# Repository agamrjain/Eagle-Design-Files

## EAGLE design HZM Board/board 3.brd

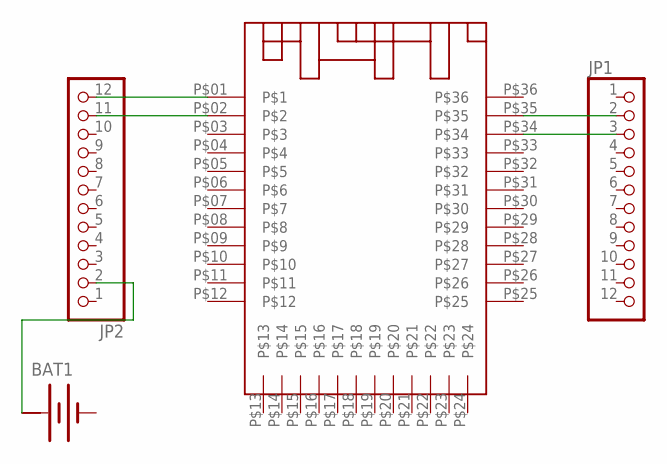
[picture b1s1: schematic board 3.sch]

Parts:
BAT1: BATTERY
JP1: PINHD-1X12; 1X12
JP2: PINHD-1X12/90; 1X12/90
U$1: HZX_MODULE; SMD_PAD_VERSION

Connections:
+: BAT1.+@1 (+)
-: BAT1.-
unnamed: BAT1.+, JP2.2
unnamed: JP2.11, U$1.P$02
unnamed: JP2.12, U$1.P$01
unnamed: JP1.2, U$1.P$35
unnamed: JP1.3, U$1.P$34

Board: 2 copper layers, 4 parts (0 on the bottom side), 5 nets, no tracks yet.

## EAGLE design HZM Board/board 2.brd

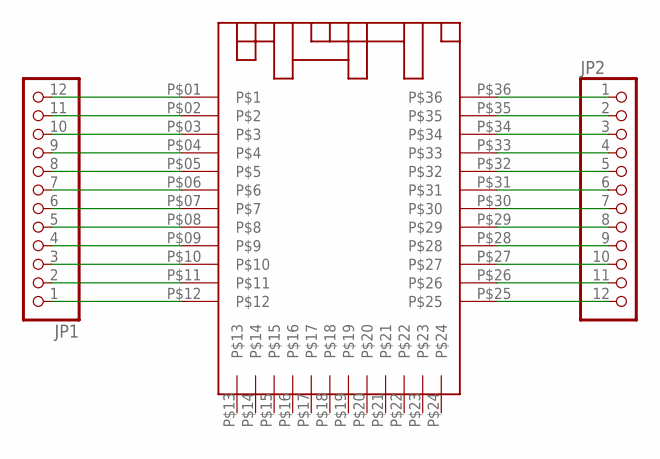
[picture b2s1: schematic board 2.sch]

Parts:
JP1, JP2: PINHD-1X12; 1X12
U$1: HZX_MODULE; SMD_PAD_VERSION

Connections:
unnamed: JP1.1, U$1.P$12
unnamed: JP1.2, U$1.P$11
unnamed: JP1.3, U$1.P$10
unnamed: JP1.4, U$1.P$09
unnamed: JP1.5, U$1.P$08
unnamed: JP1.6, U$1.P$07
unnamed: JP1.7, U$1.P$06
unnamed: JP1.8, U$1.P$05
unnamed: JP1.9, U$1.P$04
unnamed: JP1.10, U$1.P$03
unnamed: JP1.11, U$1.P$02
unnamed: JP1.12, U$1.P$01
unnamed: JP2.1, U$1.P$36
unnamed: JP2.2, U$1.P$35
unnamed: JP2.3, U$1.P$34
unnamed: JP2.4, U$1.P$33
unnamed: JP2.5, U$1.P$32
unnamed: JP2.6, U$1.P$31
unnamed: JP2.7, U$1.P$30
unnamed: JP2.8, U$1.P$29
unnamed: JP2.9, U$1.P$28
unnamed: JP2.10, U$1.P$27
unnamed: JP2.11, U$1.P$26
unnamed: JP2.12, U$1.P$25

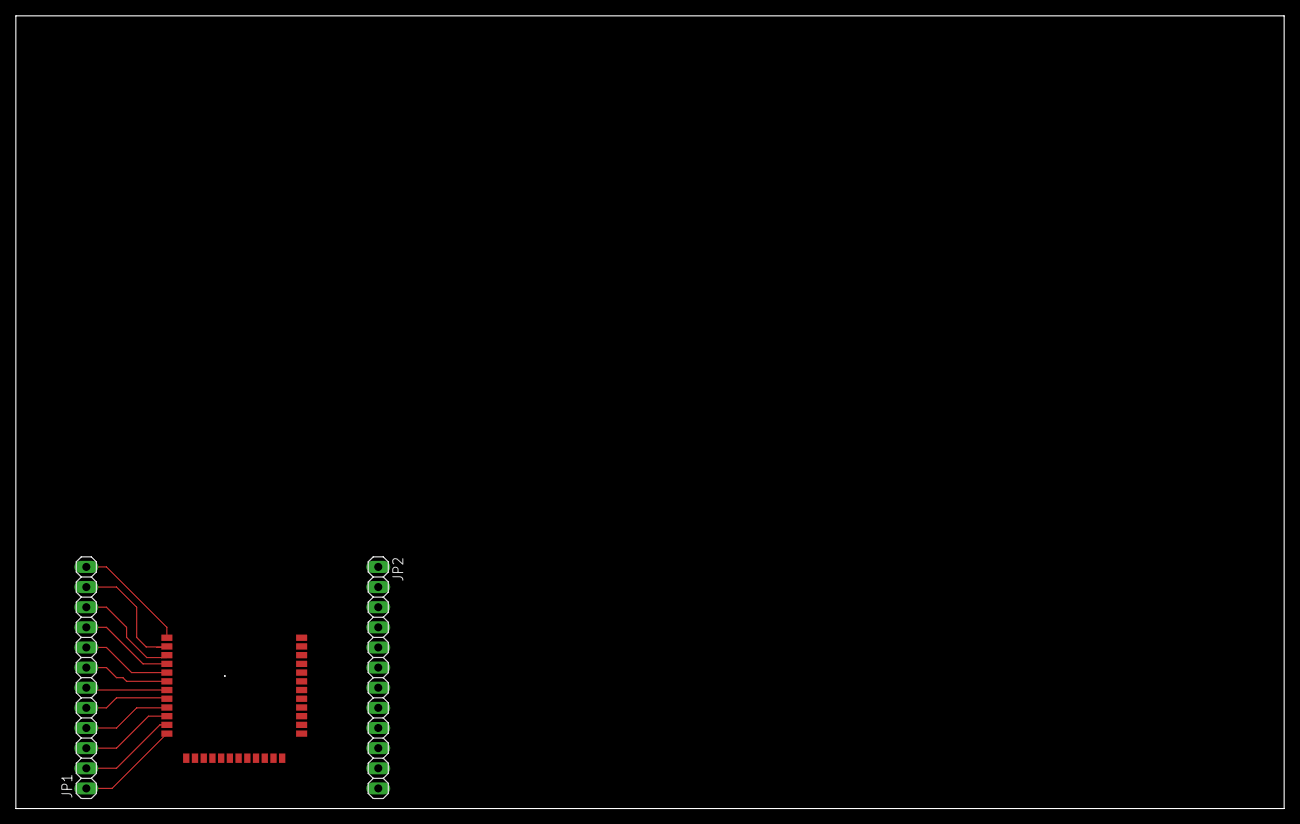
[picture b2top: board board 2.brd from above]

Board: 2 copper layers, 160.0 x 100.0 mm, 4 parts (0 on the bottom side), 24 nets.

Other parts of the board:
U$2: LOGO

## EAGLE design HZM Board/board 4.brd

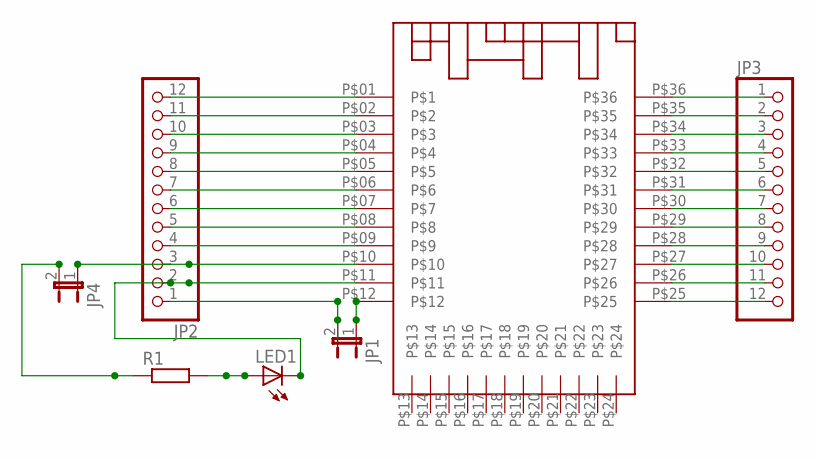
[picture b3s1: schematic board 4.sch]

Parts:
JP1, JP4: JP1E; JP1
JP2, JP3: PINHD-1X12; 1X12
LED1: LED5MM
R1: R0207/10; 0207/10
U$1: HZX_MODULE; SMD_PAD_VERSION

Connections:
unnamed: LED1.A, R1.2
unnamed: JP2.3, JP4.1, U$1.P$10
unnamed: JP2.2, LED1.K (C), U$1.P$11
unnamed: JP2.4, U$1.P$09
unnamed: JP2.5, U$1.P$08
unnamed: JP2.6, U$1.P$07
unnamed: JP2.7, U$1.P$06
unnamed: JP2.8, U$1.P$05
unnamed: JP2.9, U$1.P$04
unnamed: JP2.10, U$1.P$03
unnamed: JP2.11, U$1.P$02
unnamed: JP2.12, U$1.P$01
unnamed: JP3.1, U$1.P$36
unnamed: JP3.2, U$1.P$35
unnamed: JP3.3, U$1.P$34
unnamed: JP3.4, U$1.P$33
unnamed: JP3.5, U$1.P$32
unnamed: JP3.6, U$1.P$31
unnamed: JP3.7, U$1.P$30
unnamed: JP3.8, U$1.P$29
unnamed: JP3.9, U$1.P$28
unnamed: JP3.10, U$1.P$27
unnamed: JP3.11, U$1.P$26
unnamed: JP3.12, U$1.P$25
unnamed: JP1.2, JP2.1
unnamed: JP1.1, U$1.P$12
unnamed: JP4.2, R1.1

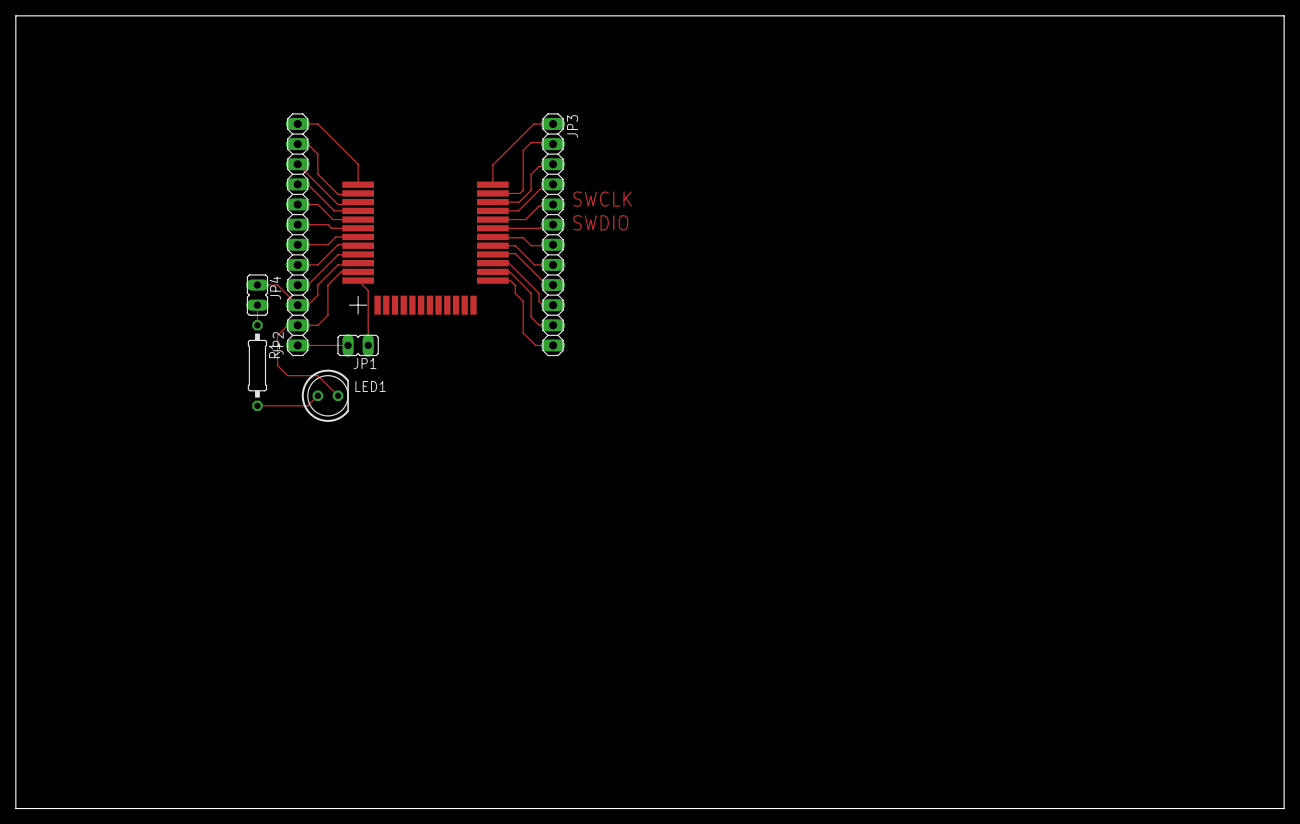
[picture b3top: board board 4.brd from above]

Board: 2 copper layers, 160.0 x 100.0 mm, 7 parts (0 on the bottom side), 27 nets.

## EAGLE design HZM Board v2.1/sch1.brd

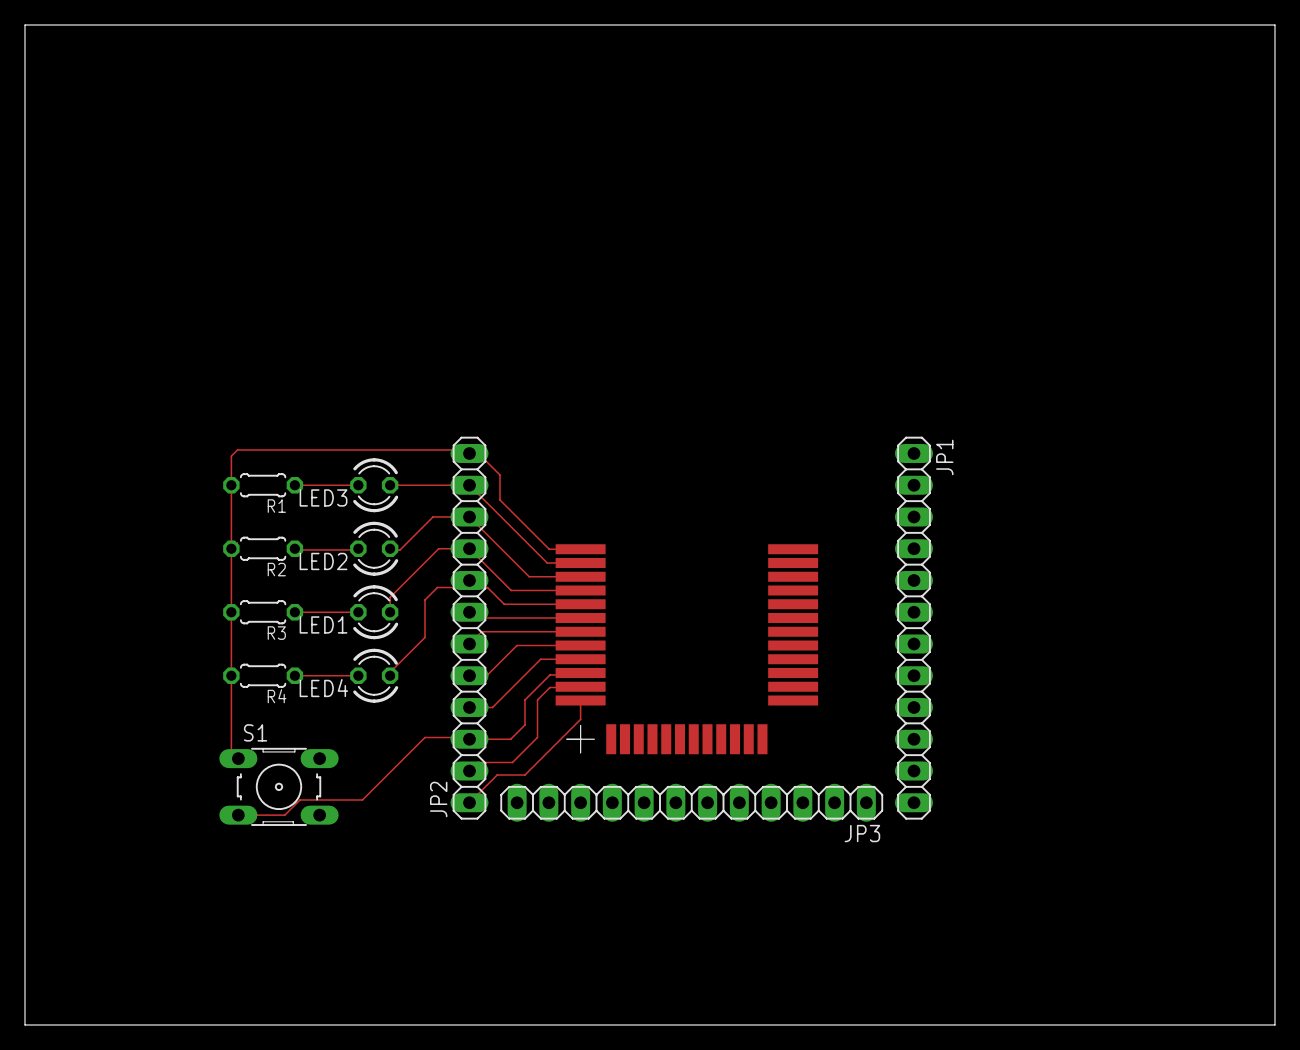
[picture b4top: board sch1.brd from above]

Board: 2 copper layers, 100.0 x 80.0 mm, 13 parts (0 on the bottom side), 40 nets.

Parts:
JP1, JP2, JP3: 1X12
LED1, LED2, LED3, LED4: LED3MM
R1, R2, R3, R4: 0204/5
S1: B3F-10XX
U$1: HZX_MODULE; SMD_PAD_VERSION

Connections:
unnamed: JP1.1, U$1.P$36
unnamed: JP1.2, U$1.P$35
unnamed: JP1.3, U$1.P$34
unnamed: JP1.4, U$1.P$33
unnamed: JP1.5, U$1.P$32
unnamed: JP1.6, U$1.P$31
unnamed: JP1.7, U$1.P$30
unnamed: JP1.8, U$1.P$29
unnamed: JP1.9, U$1.P$28
unnamed: JP1.10, U$1.P$27
unnamed: JP1.11, U$1.P$26
unnamed: JP1.12, U$1.P$25
unnamed: JP2.1, U$1.P$12
unnamed: JP2.2, U$1.P$11
unnamed: JP2.3, S1.3, U$1.P$10
unnamed: JP2.4, U$1.P$09
unnamed: JP2.5, U$1.P$08
unnamed: JP2.6, U$1.P$07
unnamed: JP2.7, U$1.P$06
unnamed: JP2.8, LED4.A, U$1.P$05
unnamed: JP2.9, LED1.A, U$1.P$04
unnamed: JP2.10, LED2.A, U$1.P$03
unnamed: JP2.11, LED3.A, U$1.P$02
unnamed: JP2.12, R1.2, R2.2, R3.2, R4.2, S1.1, U$1.P$01
unnamed: JP3.1, U$1.P$24
unnamed: JP3.2, U$1.P$23
unnamed: JP3.3, U$1.P$22
unnamed: JP3.4, U$1.P$21
unnamed: JP3.5, U$1.P$20
unnamed: JP3.6, U$1.P$19
unnamed: JP3.7, U$1.P$18
unnamed: JP3.8, U$1.P$17
unnamed: JP3.9, U$1.P$16
unnamed: JP3.10, U$1.P$15
unnamed: JP3.11, U$1.P$14
unnamed: JP3.12, U$1.P$13
unnamed: LED4.K, R4.1
unnamed: LED1.K, R3.1
unnamed: LED2.K, R2.1
unnamed: LED3.K, R1.1

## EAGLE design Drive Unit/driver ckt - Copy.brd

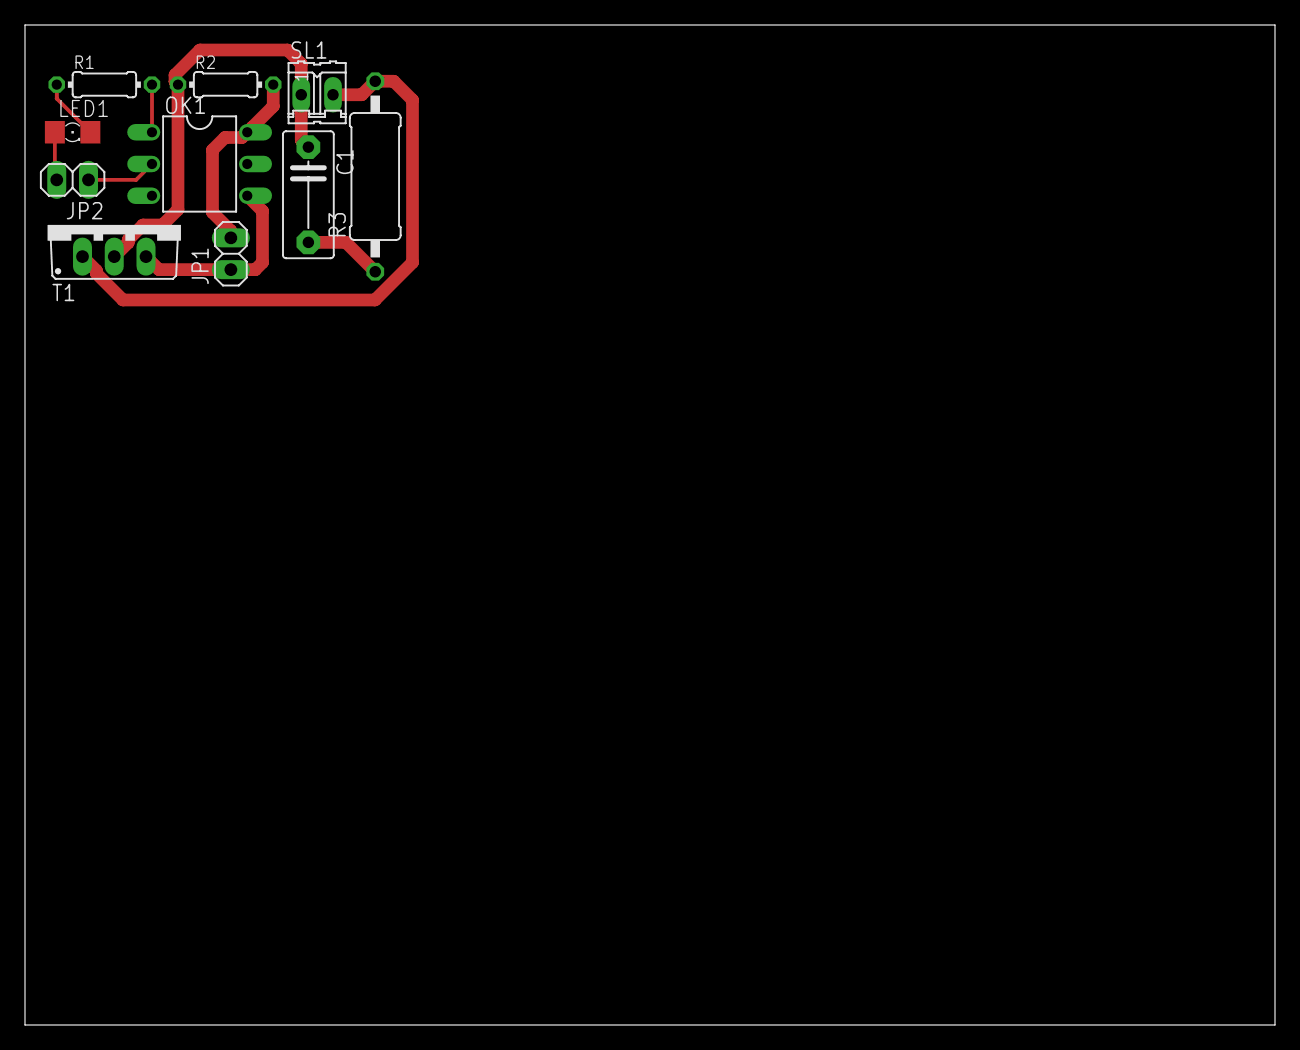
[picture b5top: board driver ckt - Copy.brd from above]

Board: 2 copper layers, 100.0 x 80.0 mm, 10 parts (0 on the bottom side), 9 nets.

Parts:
C1: C7.5B4
JP1, JP2: 1X02
LED1: LED_1206
OK1: MOC3011M; DIL06
R1, R2: 0204/7
R3: 0411/15
SL1: 02P
T1: BT138-V; TO220BV

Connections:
unnamed: LED1.C, R1.1
unnamed: OK1.1, R1.2
unnamed: JP2.2, LED1.A
unnamed: JP2.1, OK1.2
unnamed: JP1.2, OK1.6, R2.2
unnamed: JP1.1, OK1.4, T1.G
unnamed: R3.2, SL1.2, T1.T1
unnamed: C1.2, R3.1
unnamed: C1.1, R2.1, SL1.1, T1.T2

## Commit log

2018-08-27 upload#1
2018-08-27 Upload#2
2018-08-27 upload#3
2018-08-27 upload#4
2018-09-04 Add files via upload
    HZM Module library file eagle
